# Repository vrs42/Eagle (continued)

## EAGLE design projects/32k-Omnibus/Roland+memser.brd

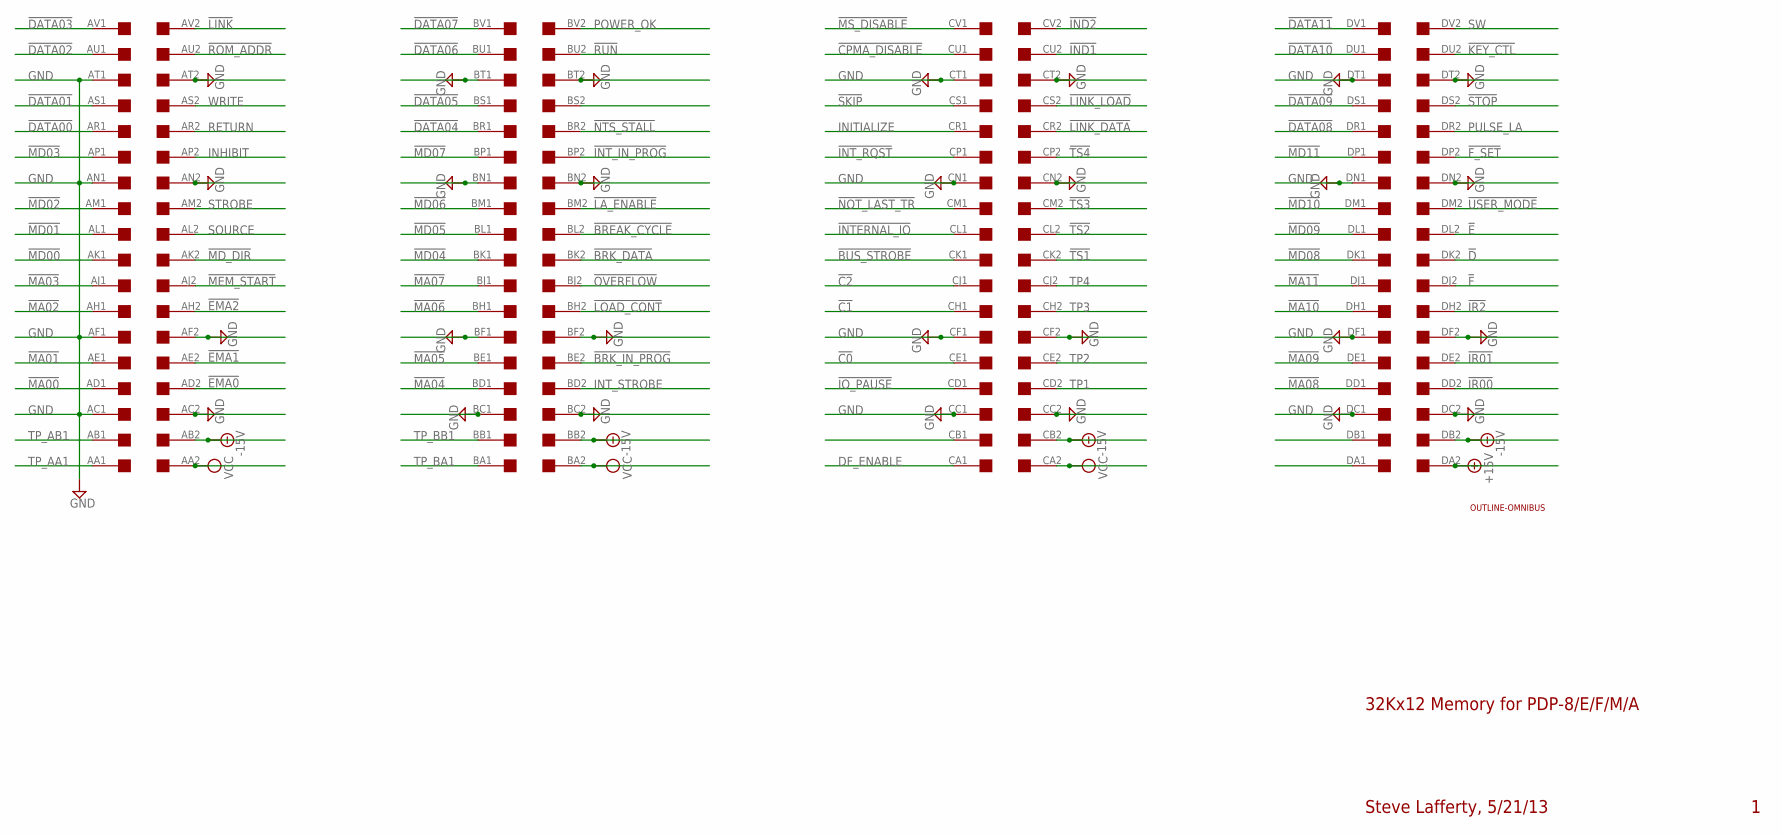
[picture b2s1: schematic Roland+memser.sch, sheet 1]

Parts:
J1: EDGE; EDGE-CON8
U$1: OUTLINE-OMNIBUS; OMNIBUS

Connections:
!BREAK_CYCLE: J1.BL2
!BRK_DATA: J1.BK2; also elsewhere on the board
!BRK_IN_PROG: J1.BE2
!BUS_STROBE: J1.CK1
!C0: J1.CE1; also elsewhere on the board
!C1: J1.CH1; also elsewhere on the board
!C2: J1.CJ1
!CPMA_DISABLE: J1.CU1; also elsewhere on the board
!D: J1.DK2; also elsewhere on the board
!DATA00: J1.AR1; also elsewhere on the board
!DATA01: J1.AS1; also elsewhere on the board
!DATA02: J1.AU1; also elsewhere on the board
!DATA03: J1.AV1; also elsewhere on the board
!DATA04: J1.BR1; also elsewhere on the board
!DATA05: J1.BS1; also elsewhere on the board
!DATA06: J1.BU1; also elsewhere on the board
!DATA07: J1.BV1; also elsewhere on the board
!DATA08: J1.DR1; also elsewhere on the board
!DATA09: J1.DS1; also elsewhere on the board
!DATA10: J1.DU1; also elsewhere on the board
!DATA11: J1.DV1; also elsewhere on the board
!E: J1.DL2
!EMA0: J1.AD2; also elsewhere on the board
!EMA1: J1.AE2; also elsewhere on the board
!EMA2: J1.AH2; also elsewhere on the board
!F: J1.DJ2; also elsewhere on the board
!F_SET: J1.DP2; also elsewhere on the board
!IND1: J1.CU2; also elsewhere on the board
!IND2: J1.CV2; also elsewhere on the board
!INTERNAL_IO: J1.CL1; also elsewhere on the board
!INT_IN_PROG: J1.BP2; also elsewhere on the board
!INT_RQST: J1.CP1; also elsewhere on the board
!IO_PAUSE: J1.CD1; also elsewhere on the board
!IR00: J1.DD2; also elsewhere on the board
!IR01: J1.DE2; also elsewhere on the board
!IR2: J1.DH2
!KEY_CTL: J1.DU2; also elsewhere on the board
!LA_ENABLE: J1.BM2; also elsewhere on the board
!LINK: J1.AV2
!LINK_DATA: J1.CR2
!LINK_LOAD: J1.CS2
!LOAD_CONT: J1.BH2; also elsewhere on the board
!MA00: J1.AD1; also elsewhere on the board
!MA01: J1.AE1; also elsewhere on the board
!MA02: J1.AH1; also elsewhere on the board
!MA03: J1.AJ1; also elsewhere on the board
!MA04: J1.BD1; also elsewhere on the board
!MA05: J1.BE1; also elsewhere on the board
!MA06: J1.BH1; also elsewhere on the board
!MA07: J1.BJ1; also elsewhere on the board
!MA08: J1.DD1; also elsewhere on the board
!MA09: J1.DE1; also elsewhere on the board
!MA10: J1.DH1; also elsewhere on the board
!MA11: J1.DJ1; also elsewhere on the board
!MD00: J1.AK1; also elsewhere on the board
!MD01: J1.AL1; also elsewhere on the board
!MD02: J1.AM1; also elsewhere on the board
!MD03: J1.AP1; also elsewhere on the board
!MD04: J1.BK1; also elsewhere on the board
!MD05: J1.BL1; also elsewhere on the board
!MD06: J1.BM1; also elsewhere on the board
!MD07: J1.BP1; also elsewhere on the board
!MD08: J1.DK1; also elsewhere on the board
!MD09: J1.DL1; also elsewhere on the board
!MD10: J1.DM1; also elsewhere on the board
!MD11: J1.DP1; also elsewhere on the board
!MD_DIR: J1.AK2; also elsewhere on the board
!MEM_START: J1.AJ2; also elsewhere on the board
!MS_DISABLE: J1.CV1; also elsewhere on the board
!NOT_LAST_TR: J1.CM1
!NTS_STALL: J1.BR2
!OVERFLOW: J1.BJ2
!ROM_ADDR: J1.AU2; also elsewhere on the board
!RUN: J1.BU2; also elsewhere on the board
!SKIP: J1.CS1; also elsewhere on the board
!STOP: J1.DS2; also elsewhere on the board
!TS1: J1.CK2; also elsewhere on the board
!TS2: J1.CL2
!TS3: J1.CM2; also elsewhere on the board
!TS4: J1.CP2; also elsewhere on the board
!USER_MODE: J1.DM2; also elsewhere on the board
+15V: J1.DA2
-15V: J1.AB2, J1.BB2, J1.CB2, J1.DB2
DF_ENABLE: J1.CA1; also elsewhere on the board
GND: J1.AC1, J1.AC2, J1.AF1, J1.AF2, J1.AN1, J1.AN2, J1.AT1, J1.AT2, J1.BC1, J1.BC2, J1.BF1, J1.BF2, J1.BN1, J1.BN2, J1.BT1, J1.BT2, J1.CC1, J1.CC2, J1.CF1, J1.CF2, J1.CN1, J1.CN2, J1.CT1, J1.CT2, J1.DC1, J1.DC2, J1.DF1, J1.DF2, J1.DN1, J1.DN2, J1.DT1, J1.DT2; also elsewhere on the board
INHIBIT: J1.AP2
INITIALIZE: J1.CR1; also elsewhere on the board
INT_STROBE: J1.BD2
POWER_OK: J1.BV2; also elsewhere on the board
PULSE_LA: J1.DR2; also elsewhere on the board
RETURN: J1.AR2
SOURCE: J1.AL2; also elsewhere on the board
STROBE: J1.AM2
SW: J1.DV2; also elsewhere on the board
TP1: J1.CD2
TP2: J1.CE2; also elsewhere on the board
TP3: J1.CH2; also elsewhere on the board
TP4: J1.CJ2; also elsewhere on the board
TP_AA1: J1.AA1; also elsewhere on the board
TP_AB1: J1.AB1; also elsewhere on the board
TP_BA1: J1.BA1; also elsewhere on the board
TP_BB1: J1.BB1; also elsewhere on the board
VCC: J1.AA2, J1.BA2, J1.CA2; also elsewhere on the board
WRITE: J1.AS2; also elsewhere on the board

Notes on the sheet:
32Kx12 Memory for PDP-8/E/F/M/A
Steve Lafferty, 5/21/13

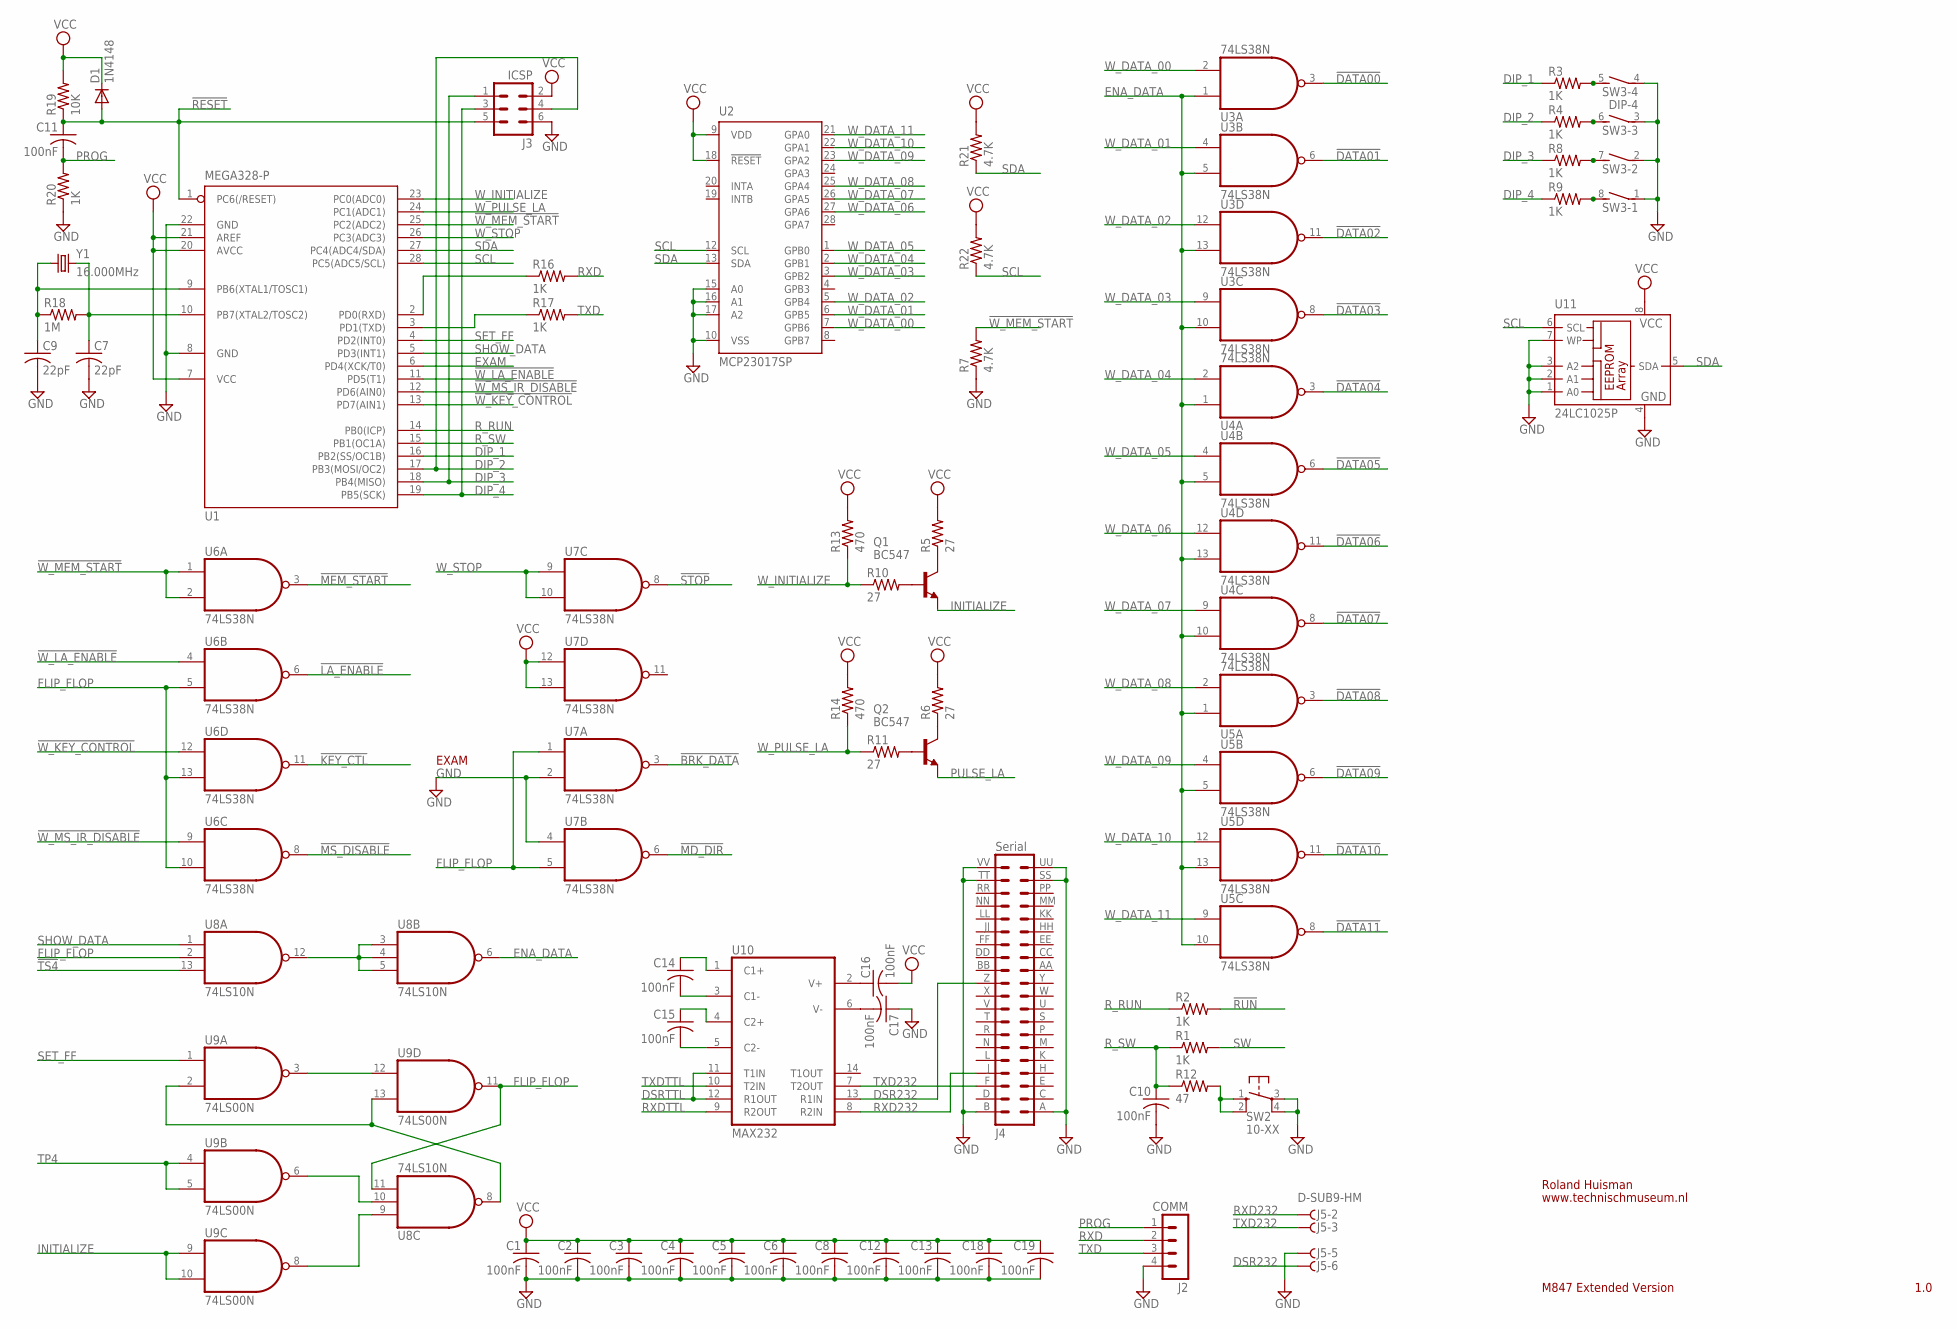
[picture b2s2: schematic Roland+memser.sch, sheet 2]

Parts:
C1, C2, C3, C4, C5, C6, C8, C10, C11, C12, C13, C14, C15, C16, C17, C18, C19: 100nF; C050-025X075
C7, C9: 22pF; C050-025X075
D1: 1N4148; DO35-10
J2: COMM; MA04-1
J3: ICSP; MA03-2
J4: Serial; DEC40PINH
J5: D-SUB9-HM; H5M09RA
Q1, Q2: BC547; TO5
R1, R2, R3, R4, R8, R9, R16, R17, R20: 1K; 0207/10
R5, R6, R10, R11: 27; 0207/10
R7, R21, R22: 4.7K; 0207/10
R12: 47; 0207/10
R13, R14: 470; 0207/10
R18: 1M; 0207/10
R19: 10K; 0207/10
SW2: 10-XX; B3F-10XX
SW3: DIP-4; DIP04S
U1: MEGA328-P; DIL28-3
U2: MCP23017SP; DIL28-3
U3, U4, U5, U6, U7: 74LS38N; DIL14
U8: 74LS10N; DIL14
U9: 74LS00N; DIL14
U10: MAX232; DIL16
U11: 24LC1025P; DIL8
Y1: 16.000MHz; HC49U-H

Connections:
!BRK_DATA: U7.3 (O); also elsewhere on the board
!DATA00: U3.3 (O); also elsewhere on the board
!DATA01: U3.6 (O); also elsewhere on the board
!DATA02: U3.11 (O); also elsewhere on the board
!DATA03: U3.8 (O); also elsewhere on the board
!DATA04: U4.3 (O); also elsewhere on the board
!DATA05: U4.6 (O); also elsewhere on the board
!DATA06: U4.11 (O); also elsewhere on the board
!DATA07: U4.8 (O); also elsewhere on the board
!DATA08: U5.3 (O); also elsewhere on the board
!DATA09: U5.6 (O); also elsewhere on the board
!DATA10: U5.11 (O); also elsewhere on the board
!DATA11: U5.8 (O); also elsewhere on the board
!KEY_CTL: U6.11 (O); also elsewhere on the board
!LA_ENABLE: U6.6 (O); also elsewhere on the board
!MD_DIR: U7.6 (O); also elsewhere on the board
!MEM_START: U6.3 (O); also elsewhere on the board
!MS_DISABLE: U6.8 (O); also elsewhere on the board
!RESET: C11.1, D1.A, J3.5, R19.1, U1.1 (PC6(/RESET))
!RUN: R2.2; also elsewhere on the board
!STOP: U7.8 (O); also elsewhere on the board
!TS4: U8.13 (I2); also elsewhere on the board
!W_KEY_CONTROL: U1.13 (PD7(AIN1)), U6.12 (I0)
!W_LA_ENABLE: U1.11 (PD5(T1)), U6.4 (I0)
!W_MEM_START: R7.2, U1.25 (PC2(ADC2)), U6.1 (I0), U6.2 (I1)
!W_MS_IR_DISABLE: U1.12 (PD6(AIN0)), U6.9 (I0)
DIP_1: R3.1, U1.16 (PB2(SS/OC1B))
DIP_2: J3.4, R4.1, U1.17 (PB3(MOSI/OC2))
DIP_3: J3.1, R8.1, U1.18 (PB4(MISO))
DIP_4: J3.3, R9.1, U1.19 (PB5(SCK))
DSR232: J4.Z (22), J5.6, U10.13 (R1IN)
DSRTTL: U10.11 (T1IN), U10.12 (R1OUT); also elsewhere on the board
ENA_DATA: U3.1 (I0), U3.5 (I1), U3.10 (I1), U3.13 (I1), U4.1 (I0), U4.5 (I1), U4.10 (I1), U4.13 (I1), U5.1 (I0), U5.5 (I1), U5.10 (I1), U5.13 (I1), U8.6 (O)
EXAM: U1.6 (PD4(XCK/T0))
FLIP_FLOP: U6.5 (I1), U6.10 (I1), U6.13 (I1), U7.1 (I0), U7.5 (I1), U8.2 (I1), U8.11 (I2), U9.11 (O)
GND: C1.2, C2.2, C3.2, C4.2, C5.2, C6.2, C7.2, C8.2, C9.2, C10.2, C12.2, C13.2, C17.1, C18.2, C19.2, J2.4, J3.6, J4.A (1), J4.B (2), J4.SS (37), J4.TT (38), J4.UU (39), J4.VV (40), J5.5, R7.1, R20.1, SW2.3, SW2.4 (P1), SW3.1, SW3.2 (1), SW3.3 (1), SW3.4 (1), U1.8 (GND), U1.22 (GND), U2.10 (VSS), U2.15 (A0), U2.16 (A1), U2.17 (A2), U3.7 (GND), U4.7 (GND), U5.7 (GND), U6.7 (GND), U7.2 (I1), U7.4 (I0), U7.7 (GND), U8.7 (GND), U9.7 (GND), U10.15 (GND), U11.1 (A0), U11.2 (A1), U11.3 (A2), U11.4 (GND), U11.7 (WP); also elsewhere on the board
INITIALIZE: Q1.1 (E), U9.9 (I0), U9.10 (I1); also elsewhere on the board
unnamed: C7.1, R18.2, U1.10 (PB7(XTAL2/TOSC2)), Y1.1
unnamed: C9.1, R18.1, U1.9 (PB6(XTAL1/TOSC1)), Y1.2
unnamed: Q1.3 (C), R5.1
unnamed: Q1.2 (B), R10.2
unnamed: Q2.3 (C), R6.1
unnamed: Q2.2 (B), R11.2
unnamed: U9.3 (O), U9.12 (I0)
unnamed: U8.3 (I0), U8.4 (I1), U8.5 (I2), U8.12 (O)
unnamed: U8.8 (O), U9.2 (I1), U9.13 (I1)
unnamed: R17.1, U1.3 (PD1(TXD))
unnamed: R16.1, U1.2 (PD0(RXD))
unnamed: U8.10 (I1), U9.6 (O)
unnamed: U8.9 (I0), U9.8 (O)
unnamed: C17.2, U10.6 (V-)
unnamed: C14.1, U10.1 (C1+)
unnamed: C14.2, U10.3 (C1-)
unnamed: C15.2, U10.5 (C2-)
unnamed: C15.1, U10.4 (C2+)
unnamed: C16.1, U10.2 (V+)
unnamed: R12.2, SW2.1 (S), SW2.2 (S1)
unnamed: R3.2, SW3.5 (2)
unnamed: R4.2, SW3.6 (2)
unnamed: R8.2, SW3.7 (2)
unnamed: R9.2, SW3.8 (2)
PROG: C11.2, J2.1, R20.2; also elsewhere on the board
PULSE_LA: Q2.1 (E); also elsewhere on the board
RXD: J2.2, R16.2; also elsewhere on the board
RXD232: J4.J (8), J5.2, U10.8 (R2IN)
RXDTTL: U10.9 (R2OUT); also elsewhere on the board
R_RUN: R2.1, U1.14 (PB0(ICP))
R_SW: C10.1, R1.1, R12.1, U1.15 (PB1(OC1A))
SCL: R22.1, U1.28 (PC5(ADC5/SCL)), U2.12 (SCL), U11.6 (SCL)
SDA: R21.1, U1.27 (PC4(ADC4/SDA)), U2.13 (SDA), U11.5 (SDA)
SET_FF: U1.4 (PD2(INT0)), U9.1 (I0)
SHOW_DATA: U1.5 (PD3(INT1)), U8.1 (I0)
SW: R1.2; also elsewhere on the board
TP4: U9.4 (I0), U9.5 (I1); also elsewhere on the board
TXD: J2.3, R17.2; also elsewhere on the board
TXD232: J4.F (6), J5.3, U10.7 (T2OUT)
TXDTTL: U10.10 (T2IN); also elsewhere on the board
VCC: C1.1, C2.1, C3.1, C4.1, C5.1, C6.1, C8.1, C12.1, C13.1, C16.2, C18.1, C19.1, D1.C, J3.2, R5.2, R6.2, R13.2, R14.2, R19.2, R21.2, R22.2, U1.7 (VCC), U1.20 (AVCC), U1.21 (AREF), U2.9 (VDD), U2.18 (!RESET), U3.14 (VCC), U4.14 (VCC), U5.14 (VCC), U6.14 (VCC), U7.12 (I0), U7.13 (I1), U7.14 (VCC), U8.14 (VCC), U9.14 (VCC), U10.16 (VCC), U11.8 (VCC); also elsewhere on the board
W_DATA_00: U2.7 (GPB6), U3.2 (I1)
W_DATA_01: U2.6 (GPB5), U3.4 (I0)
W_DATA_02: U2.5 (GPB4), U3.12 (I0)
W_DATA_03: U2.3 (GPB2), U3.9 (I0)
W_DATA_04: U2.2 (GPB1), U4.2 (I1)
W_DATA_05: U2.1 (GPB0), U4.4 (I0)
W_DATA_06: U2.27 (GPA6), U4.12 (I0)
W_DATA_07: U2.26 (GPA5), U4.9 (I0)
W_DATA_08: U2.25 (GPA4), U5.2 (I1)
W_DATA_09: U2.23 (GPA2), U5.4 (I0)
W_DATA_10: U2.22 (GPA1), U5.12 (I0)
W_DATA_11: U2.21 (GPA0), U5.9 (I0)
W_INITIALIZE: R10.1, R13.1, U1.23 (PC0(ADC0))
W_PULSE_LA: R11.1, R14.1, U1.24 (PC1(ADC1))
W_STOP: U1.26 (PC3(ADC3)), U7.9 (I0), U7.10 (I1)

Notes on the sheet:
D-SUB9-HM
M847 Extended Version
Roland Huisman
1.0
www.technischmuseum.nl
EXAM

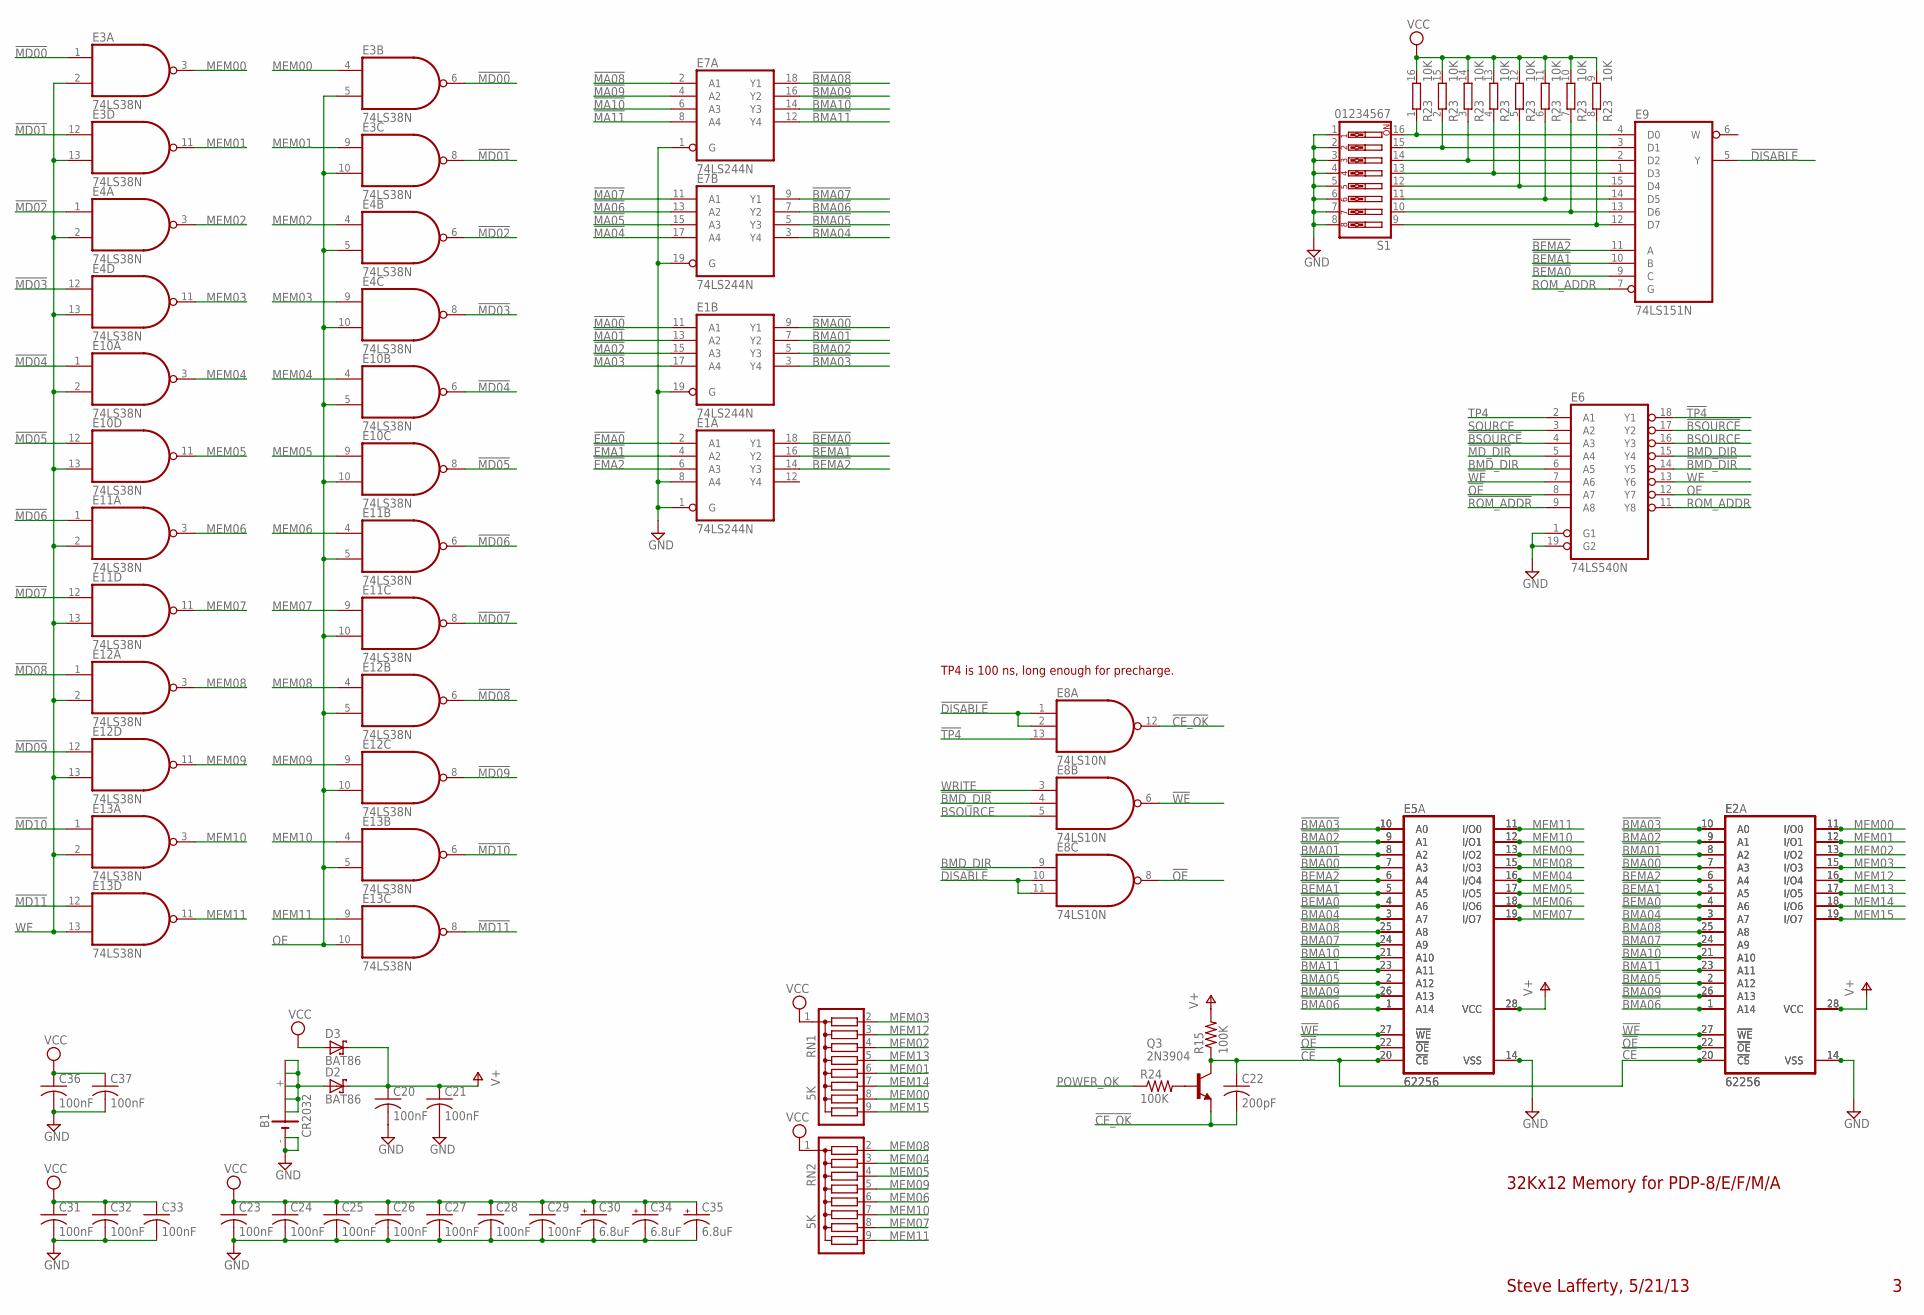
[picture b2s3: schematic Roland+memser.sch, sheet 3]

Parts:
B1: CR2032; B2430UNI
C20, C21, C23, C24, C25, C26, C27, C28, C29, C31, C32, C33, C36, C37: 100nF; C050-025X075
C22: 200pF; C050-025X075
C30, C34, C35: 6.8uF; E12-8
D2, D3: BAT86; DO35-10
E1, E7: 74LS244N; DIL20
E2, E5: 62256; DIL28-6
E2A, E5A: 62256; DIL28-3
E3, E4, E10, E11, E12, E13: 74LS38N; DIL14
E6: 74LS540N; DIL20
E8: 74LS10N; DIL14
E9: 74LS151N; DIL16
Q3: 2N3904; TO92
R15, R24: 100K; 0207/10
R23: 10K; DIL16
RN1, RN2: 5K; SIL9
S1: 01234567; EDG-08

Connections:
!BEMA0: E1.18 (Y1), E2.4 (A6), E2A.4 (A6), E5.4 (A6), E5A.4 (A6), E9.9 (C)
!BEMA1: E1.16 (Y2), E2.5 (A5), E2A.5 (A5), E5.5 (A5), E5A.5 (A5), E9.10 (B)
!BEMA2: E1.14 (Y3), E2.6 (A4), E2A.6 (A4), E5.6 (A4), E5A.6 (A4), E9.11 (A)
!BMA00: E1.9 (Y1), E2.7 (A3), E2A.7 (A3), E5.7 (A3), E5A.7 (A3)
!BMA01: E1.7 (Y2), E2.8 (A2), E2A.8 (A2), E5.8 (A2), E5A.8 (A2)
!BMA02: E1.5 (Y3), E2.9 (A1), E2A.9 (A1), E5.9 (A1), E5A.9 (A1)
!BMA03: E1.3 (Y4), E2.10 (A0), E2A.10 (A0), E5.10 (A0), E5A.10 (A0)
!BMA04: E2.3 (A7), E2A.3 (A7), E5.3 (A7), E5A.3 (A7), E7.3 (Y4)
!BMA05: E2.2 (A12), E2A.2 (A12), E5.2 (A12), E5A.2 (A12), E7.5 (Y3)
!BMA06: E2.1 (A14), E2A.1 (A14), E5.1 (A14), E5A.1 (A14), E7.7 (Y2)
!BMA07: E2.24 (A9), E2A.24 (A9), E5.24 (A9), E5A.24 (A9), E7.9 (Y1)
!BMA08: E2.25 (A8), E2A.25 (A8), E5.25 (A8), E5A.25 (A8), E7.18 (Y1)
!BMA09: E2.26 (A13), E2A.26 (A13), E5.26 (A13), E5A.26 (A13), E7.16 (Y2)
!BMA10: E2.21 (A10), E2A.21 (A10), E5.21 (A10), E5A.21 (A10), E7.14 (Y3)
!BMA11: E2.23 (A11), E2A.23 (A11), E5.23 (A11), E5A.23 (A11), E7.12 (Y4)
!BMD_DIR: E6.14 (Y5), E8.4 (I1)
!BSOURCE: E6.4 (A3), E6.17 (Y2)
!CE: C22.1, E2.20 (!CE), E2A.20 (!CS), E5.20 (!CE), E5A.20 (!CS), Q3.1 (C), R15.1
!CE_OK: C22.2, E8.12 (O), Q3.3 (E)
!DISABLE: E8.1 (I0), E8.2 (I1), E8.10 (I1), E8.11 (I2), E9.5 (Y)
!EMA0: E1.2 (A1); also elsewhere on the board
!EMA1: E1.4 (A2); also elsewhere on the board
!EMA2: E1.6 (A3); also elsewhere on the board
!MA00: E1.11 (A1); also elsewhere on the board
!MA01: E1.13 (A2); also elsewhere on the board
!MA02: E1.15 (A3); also elsewhere on the board
!MA03: E1.17 (A4); also elsewhere on the board
!MA04: E7.17 (A4); also elsewhere on the board
!MA05: E7.15 (A3); also elsewhere on the board
!MA06: E7.13 (A2); also elsewhere on the board
!MA07: E7.11 (A1); also elsewhere on the board
!MA08: E7.2 (A1); also elsewhere on the board
!MA09: E7.4 (A2); also elsewhere on the board
!MA10: E7.6 (A3); also elsewhere on the board
!MA11: E7.8 (A4); also elsewhere on the board
!MD00: E3.1 (I0), E3.6 (O); also elsewhere on the board
!MD01: E3.8 (O), E3.12 (I0); also elsewhere on the board
!MD02: E4.1 (I0), E4.6 (O); also elsewhere on the board
!MD03: E4.8 (O), E4.12 (I0); also elsewhere on the board
!MD04: E10.1 (I0), E10.6 (O); also elsewhere on the board
!MD05: E10.8 (O), E10.12 (I0); also elsewhere on the board
!MD06: E11.1 (I0), E11.6 (O); also elsewhere on the board
!MD07: E11.8 (O), E11.12 (I0); also elsewhere on the board
!MD08: E12.1 (I0), E12.6 (O); also elsewhere on the board
!MD09: E12.8 (O), E12.12 (I0); also elsewhere on the board
!MD10: E13.1 (I0), E13.6 (O); also elsewhere on the board
!MD11: E13.8 (O), E13.12 (I0); also elsewhere on the board
!MD_DIR: E6.5 (A4); also elsewhere on the board
!OE: E2.22 (!OE), E2A.22 (!OE), E5.22 (!OE), E5A.22 (!OE), E6.8 (A7), E8.8 (O)
!ROM_ADDR: E6.9 (A8); also elsewhere on the board
!TP4: E6.18 (Y1), E8.13 (I2)
!WE: E2.27 (!WE), E2A.27 (!WE), E5.27 (!WE), E5A.27 (!WE), E6.7 (A6), E8.6 (O)
BMD_DIR: E6.6 (A5), E6.15 (Y4), E8.9 (I0)
BSOURCE: E6.16 (Y3), E8.5 (I2)
GND: B1.-, B1.-@1 (-), C20.2, C21.2, C23.2, C24.2, C25.2, C26.2, C27.2, C28.2, C29.2, C30.-, C31.2, C32.2, C33.2, C34.-, C35.-, C36.2, C37.2, E1.1 (G), E1.8 (A4), E1.10 (GND), E1.19 (G), E2.14 (VSS), E2A.14 (VSS), E3.7 (GND), E4.7 (GND), E5.14 (VSS), E5A.14 (VSS), E6.1 (G1), E6.10 (GND), E6.19 (G2), E7.1 (G), E7.10 (GND), E7.19 (G), E8.7 (GND), E9.8 (GND), E10.7 (GND), E11.7 (GND), E12.7 (GND), E13.7 (GND), S1.1, S1.2, S1.3, S1.4, S1.5, S1.6, S1.7, S1.8; also elsewhere on the board
MEM00: E2.11 (I/O0), E2A.11 (I/O0), E3.3 (O), E3.4 (I0), RN1.8
MEM01: E2.12 (I/O1), E2A.12 (I/O1), E3.9 (I0), E3.11 (O), RN1.6
MEM02: E2.13 (I/O2), E2A.13 (I/O2), E4.3 (O), E4.4 (I0), RN1.4
MEM03: E2.15 (I/O3), E2A.15 (I/O3), E4.9 (I0), E4.11 (O), RN1.2
MEM04: E5.16 (I/O4), E5A.16 (I/O4), E10.3 (O), E10.4 (I0), RN2.3
MEM05: E5.17 (I/O5), E5A.17 (I/O5), E10.9 (I0), E10.11 (O), RN2.4
MEM06: E5.18 (I/O6), E5A.18 (I/O6), E11.3 (O), E11.4 (I0), RN2.6
MEM07: E5.19 (I/O7), E5A.19 (I/O7), E11.9 (I0), E11.11 (O), RN2.8
MEM08: E5.15 (I/O3), E5A.15 (I/O3), E12.3 (O), E12.4 (I0), RN2.2
MEM09: E5.13 (I/O2), E5A.13 (I/O2), E12.9 (I0), E12.11 (O), RN2.5
MEM10: E5.12 (I/O1), E5A.12 (I/O1), E13.3 (O), E13.4 (I0), RN2.7
MEM11: E5.11 (I/O0), E5A.11 (I/O0), E13.9 (I0), E13.11 (O), RN2.9
MEM12: E2.16 (I/O4), E2A.16 (I/O4), RN1.3
MEM13: E2.17 (I/O5), E2A.17 (I/O5), RN1.5
MEM14: E2.18 (I/O6), E2A.18 (I/O6), RN1.7
MEM15: E2.19 (I/O7), E2A.19 (I/O7), RN1.9
unnamed: B1.+, B1.+@1 (+), B1.+@2 (+), B1.+@3 (+), B1.+@4 (+), D2.A
unnamed: E9.1 (D3), R23.4 (1), S1.13
unnamed: E9.2 (D2), R23.3 (1), S1.14
unnamed: E9.15 (D4), R23.5 (1), S1.12
unnamed: E9.14 (D5), R23.6 (1), S1.11
unnamed: E9.13 (D6), R23.7 (1), S1.10
unnamed: E9.12 (D7), R23.8 (1), S1.9
unnamed: E9.4 (D0), R23.1, S1.16
unnamed: E9.3 (D1), R23.2 (1), S1.15
unnamed: Q3.2 (B), R24.2
OE: E3.5 (I1), E3.10 (I1), E4.5 (I1), E4.10 (I1), E6.12 (Y7), E10.5 (I1), E10.10 (I1), E11.5 (I1), E11.10 (I1), E12.5 (I1), E12.10 (I1), E13.5 (I1), E13.10 (I1)
POWER_OK: R24.1; also elsewhere on the board
ROM_ADDR: E6.11 (Y8), E9.7 (G)
SOURCE: E6.3 (A2); also elsewhere on the board
TP4: E6.2 (A1); also elsewhere on the board
V+: C20.1, C21.1, D2.C, D3.C, E2.28 (VCC), E2A.28 (VCC), E5.28 (VCC), E5A.28 (VCC), R15.2
VCC: C23.1, C24.1, C25.1, C26.1, C27.1, C28.1, C29.1, C30.+, C31.1, C32.1, C33.1, C34.+, C35.+, C36.1, C37.1, D3.A, E1.20 (VCC), E3.14 (VCC), E4.14 (VCC), E6.20 (VCC), E7.20 (VCC), E8.14 (VCC), E9.16 (VCC), E10.14 (VCC), E11.14 (VCC), E12.14 (VCC), E13.14 (VCC), R23.9 (2), R23.10 (2), R23.11 (2), R23.12 (2), R23.13 (2), R23.14 (2), R23.15 (2), R23.16 (2), RN1.1, RN2.1; also elsewhere on the board
WE: E3.2 (I1), E3.13 (I1), E4.2 (I1), E4.13 (I1), E6.13 (Y6), E10.2 (I1), E10.13 (I1), E11.2 (I1), E11.13 (I1), E12.2 (I1), E12.13 (I1), E13.2 (I1), E13.13 (I1)
WRITE: E8.3 (I0); also elsewhere on the board

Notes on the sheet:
32Kx12 Memory for PDP-8/E/F/M/A
Steve Lafferty, 5/21/13
TP4 is 100 ns, long enough for precharge.

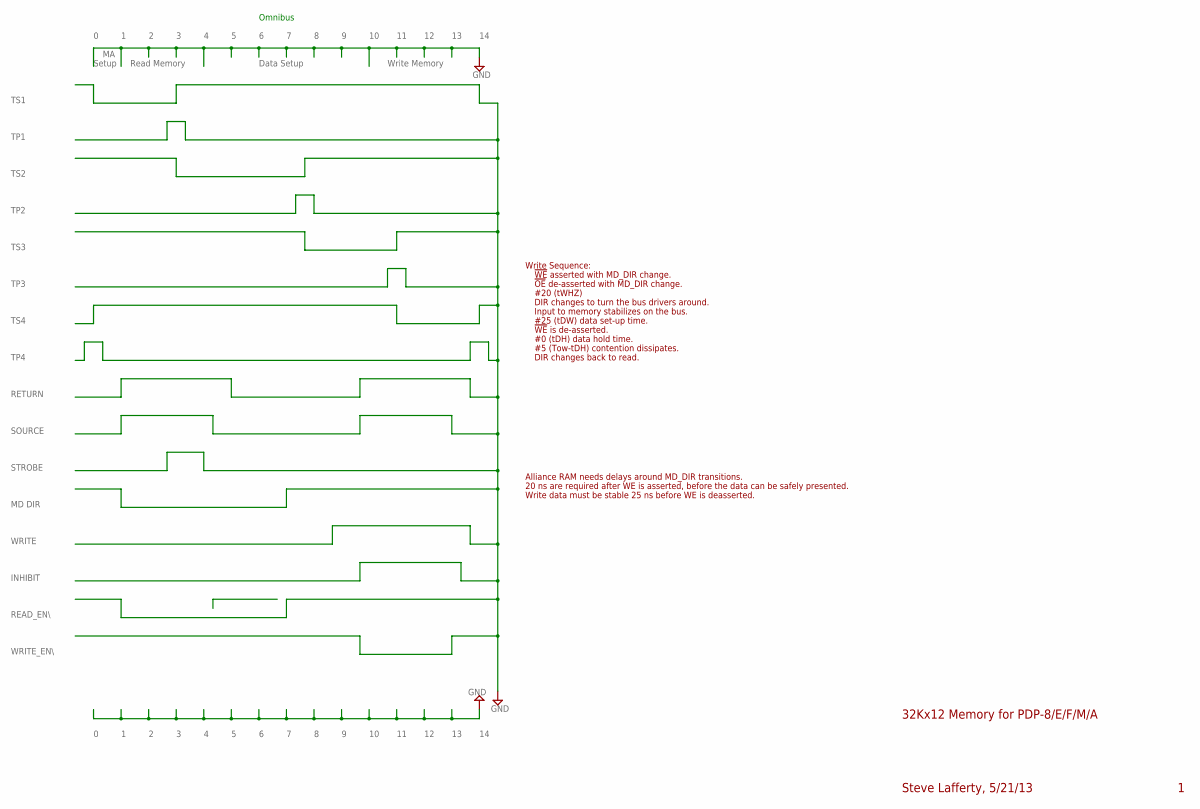
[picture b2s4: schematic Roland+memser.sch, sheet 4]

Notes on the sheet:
TS1
TS2
TS3
TS4
TP1
TP2
TP3
TP4
INHIBIT
WRITE
STROBE
SOURCE
RETURN
MD DIR
Setup
Read Memory
Data Setup
Write Memory
Omnibus
READ_EN\\
WRITE_EN\\
32Kx12 Memory for PDP-8/E/F/M/A
Steve Lafferty, 5/21/13
Alliance RAM needs delays around MD_DIR transitions.
20 ns are required after WE is asserted, before the data can be safely presented.
Write data must be stable 25 ns before WE is deasserted.
Write Sequence:
!WE! asserted with MD_DIR change.
!OE! de-asserted with MD_DIR change.
#20 (tWHZ)
DIR changes to turn the bus drivers around.
Input to memory stabilizes on the bus.
#25 (tDW) data set-up time.
!WE! is de-asserted.
#0 (tDH) data hold time.
#5 (Tow-tDH) contention dissipates.
DIR changes back to read.
